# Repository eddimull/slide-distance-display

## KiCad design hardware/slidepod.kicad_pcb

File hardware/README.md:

# SlidePod: wireless trombone slide sensor

A single clip-on pod for the stationary inner slide. It measures slide extension with a
VL53L1X time-of-flight sensor and pitch with an LSM6DS3TR-C accelerometer that picks up
the slide tube's vibration (rev 0.2; rev 0.1 used a piezo contact pickup). It sends position,
pitch and partial over BLE to the Flutter app. There is no screen and no wire to the bell.

## Mechanical constraint that shapes the board

The VL53L1X emits **perpendicular to the PCB**. For the beam to run down the slide, the
board stands as a thin "fin" perpendicular to the slide tubes:

```
        side view (slide runs left → right)

            ┌──┐  ← antenna end (top, away from brass)
            │  │
     PCB →  │  │──►  ToF beam toward the reflector tab on the outer handle brace
   (fin)    │  │
            │▓▓│  ← battery behind the board
     ═══════╧══╧═════════ inner slide tube (clamp at bottom)
```

- The ToF sits on the **front face** with nothing taller than it nearby. The ESP32 module,
  USB-C, switch and battery connector go on the back or sides.
- The module antenna sits at the top edge, as far from the brass as possible, with copper
  keep-out on all layers under and around it per the Espressif guidelines.
- The accelerometer is soldered to the board, which the clamp holds against the tube, so the
  tube's vibration reaches it through the mount. No wired pickup.

Current outline (rev 0.2): **32 × 26 mm**, 4-layer, 1.0 mm thick, **double-sided assembly** (the front holds only what must be seen or reached; the rest is on the back). Rev 0.1 was 30 × 50 mm, single-sided. Ordering steps: `fab/JLCPCB_ORDER.md`.

## Block diagram

```
USB-C ─ESD─┬─ D+/D- ──────────────────────────────► ESP32-S3 GPIO19/20 (native USB)
           └─ VBUS ─┬─► MCP73831 ──► VBAT ─┐
                    │                       ├─(power path)─► SW ─► VSYS ─► ME6211 ─► 3V3
                    └──────── Schottky ─────┘   P-FET from VBAT, gated by VBUS
JST-PH (1S LiPo with protection PCB) ─► VBAT

3V3 ─► ESP32-S3-MINI-1, VL53L1X, LSM6DS3TR-C, status LEDs
```

## Pin map (ESP32-S3-MINI-1)

| Net | GPIO | Notes |
|---|---|---|
| VBAT_SENSE | 2 | ADC1_CH1, 1M/1M divider from VBAT + 100 nF (about 2 µA drain) |
| TOF_INT | 4 | VL53L1X GPIO1 (open-drain, 10k pull-up) |
| TOF_XSHUT | 5 | 10k pull-up; drive low to power the sensor down |
| I2C_SDA | 8 | 4.7k pull-up |
| I2C_SCL | 9 | 4.7k pull-up |
| VBUS_SENSE | 10 | 100k/100k divider from VBUS (5 V → 2.5 V): USB present |
| LED_R / LED_G / LED_B | 11 / 12 / 13 | Three 0603 LEDs, anodes to 3V3, active-low, LEDC PWM |
| USB_D- / USB_D+ | 19 / 20 | Built-in USB-Serial/JTAG for flashing and logs |
| BOOT | 0 | Tactile switch to GND, 10k pull-up |
| EN | EN | 10k pull-up + 1 µF to GND, RESET switch to GND |
| U0TXD / U0RXD | 43 / 44 | Test pads only |

Rev 0.2 moves the sensor and LED lines to the module's right edge and splits I2C into two
buses (the shared bus could not be routed past the LEDs). The pins were reassigned during
layout; `tools/circuit.py` (`esp`) is the source of truth and `src/slidepod/main.cpp` must match:

| Net (rev 0.2) | GPIO | Module pin |
|---|---|---|
| LED_R / LED_G / LED_B | 42 / 41 / 40 | 38 / 37 / 36 |
| TOF_SCL / TOF_SDA | 39 / 38 | 35 / 34 (ToF bus, Wire, 4.7k pull-ups R16/R15) |
| TOF_INT / TOF_XSHUT | 37 / 36 | 33 / 32 |
| IMU_SCL / IMU_SDA | 35 / 48 | 31 / 30 (IMU bus, Wire1, 4.7k pull-ups R20/R19) |
| IMU_INT | 34 | 29 (LSM6DS3TR-C INT1) |

Avoided: strapping pins 3, 45, 46, and ADC2, which conflicts with the radio.

**Why discrete LEDs and not a WS2812:** the system runs at 3.3 V, below the WS2812's
rated supply. A WS2812 also draws about 1 mA even when off, while discrete LEDs on LEDC
draw nothing.

## Circuit blocks

### Power
- **USB-C receptacle (16-pin):** CC1 and CC2 each get 5.1k to GND (UFP, 5 V default).
  USBLC6-2SC6 on D+/D-/VBUS.
- **MCP73831T-2ACI/OT charger:** 4.2 V. R_PROG = 3.3k sets I_chg = 1000 V / 3.3 kΩ ≈ 300 mA
  (about 0.75C for a 400 mAh cell). 4.7 µF on VBUS and on VBAT.
- **Power path:** a Schottky diode from VBUS feeds VSYS. A P-MOSFET (gate to VBUS, 100k
  gate pull-down) connects VBAT to VSYS when USB is absent. This way the charger never
  sees the system load.
- **Power switch:** an SMD slide switch in series with VSYS. The battery still charges with the switch off.
- **Charge LED:** an orange LED on MCP73831 STAT (lit while charging). STAT is not wired to the ESP32, so an unpowered ESP32 is never back-fed through it.
- **ME6211C33 LDO:** 500 mA, enough for ESP32-S3 radio peaks of about 350 mA. 10 µF in and 10 µF out.
- **Battery:** 1S LiPo, 300–500 mAh, **with a protection PCB** (this board doesn't add protection).

### ESP32-S3-MINI-1
- 3V3 on all supply pins, with 10 µF + 100 nF near the module, plus 100 nF at each supply pin group.
- All GND pads go to a solid ground plane on layer 2, stitched with vias.

### VL53L1X
- AVDD and AVDDVCSEL to 3V3, each with 100 nF, plus 4.7 µF bulk.
- I2C address 0x29. XSHUT and GPIO1 as in the pin map.
- Enclosure: an open aperture in front of the sensor, or an IR-transparent cover window
  spaced per ST AN4907. Run crosstalk calibration in firmware if there's a cover.

### Pitch pickup (rev 0.2)
The piezo front end (MCP6001 amplifier, bias divider, clamp diode, anti-alias RC and the J3
solder pads) was removed. The LSM6DS3TR-C on its own I2C bus (0x6A, INT1 on IO34) replaces it:
FIFO-buffered acceleration at up to 6.66 kHz covers the slide-tube fundamentals.

### Indicator and controls
- Three separate 0603 LEDs (red, green, blue), side by side for a light pipe. Series resistors: 1k red (about 1.3 mA), 33 Ω green and blue (about 3–9 mA, depending on Vf at 3.3 V). Balance brightness with PWM in firmware.
  A combined RGB package was dropped because no JLC common-anode part had a pinout I could verify.
- BOOT and RESET tactile switches on the board edge, which the enclosure can expose as pinholes.

### Test points
3V3, VSYS, VBAT, GND, U0TXD, U0RXD (rev 0.2 adds EN and BOOT; TP5 went with the piezo).

## Key parts (JLCPCB / LCSC)

Check live stock and the Basic/Extended label on jlcpcb.com/partdetail/<C#> before ordering.

| Ref | Part | LCSC | Status |
|---|---|---|---|
| U1 | ESP32-S3-MINI-1-N8 | C2913206 | Extended. Alternate: N4R2 C3013941 (PSRAM, not needed) |
| U2 | VL53L1CXV0FY/1 | C190004 | Not yet confirmed on JLC |
| U3 | MCP73831T-2ACI/OT | C424093 | Not yet confirmed |
| U4 | ME6211C33M5G-N | C82942 | Extended. Alternate: AP2112K-3.3 C51118 |
| U6 | USBLC6-2SC6 (ST) | C7519 | Extended |
| J1 | TYPE-C-31-M-12 | C165948 | Extended |
| J2 | JST S2B-PH-SM4-TB | C295747 | Extended |
| SW1/2 | TS-1187A-B-A-B | C318884 | Not yet confirmed |
| SW3 | MSK12C02 | C431540 | Not yet confirmed |
| Q1 | AO3401A | C15127 | Basic |
| D2 | B5819W (CJ) | C8598 | Basic |
| LED1, D3 | KT-0603R red | C2286 | Basic |
| LED2 / LED3 | KT-0603G green / KT-0603B blue | C12624 / C2288 | Extended (no Basic green or blue 0603 LEDs at JLC) |
| R, C | 0402 resistors and capacitors (4.7 µF and 10 µF are 0603) | see `LCSC_R0402` / `LCSC_C` in `tools/circuit.py` | Basic |

## Firmware-facing summary
- I2C @ 400 kHz on GPIO8/9. VL53L1X in Short mode, 20 ms budget, 8×8 ROI.
- Rev 0.2 (build with `-DSLIDEPOD_REV=2`): ToF on Wire (SDA IO38 / SCL IO39); LSM6DS3TR-C (0x6A) on a second bus, Wire1 (SDA IO48 / SCL IO35), INT1 on IO34 for FIFO watermark.
- BLE GATT notify at 50 Hz with about 10 bytes per update. Calibration (offset, length) goes in a writable characteristic.

## Design files and workflow

The schematic and board are **generated** from Python, so changes are reviewable as code:

| File | Role |
|---|---|
| `tools/circuit.py` | **Source of truth:** parts, values, footprints, LCSC numbers, pin-to-net map |
| `tools/gen_sch.py` | Builds `slidepod.kicad_sch` (a net label on every pin, using KiCad library symbols) |
| `tools/gen_pcb.py` | Builds `slidepod.kicad_pcb`: outline, 4-layer stackup, net classes, placement, GND pours |
| `tools/check_net.py` | Checks the exported netlist against `circuit.py`, pin by pin |
| `tools/kicad.sh` | Runs any command in KiCad 10 under Docker (`kicad/kicad:10.0` plus numpy, built from `tools/Dockerfile` on first use) |

```sh
make            # ERC, netlist check against circuit.py, DRC with schematic parity
make pcb        # re-place the board (DISCARDS routing; use only before routing)
make route      # fan-out, Freerouting, finish, stitch (about 30 min)
make fab        # Gerbers, drill, BOM, CPL into fab/
make pdf        # schematic PDF
```

**Placement:** anchor parts (module, ToF, connectors, buttons, LED) have fixed positions
in `ANCHORS`. Everything else is packed to the nearest free spot beside the pins it
connects to. Parts excluded from placement:

- the antenna band (top 6.6 mm), via the module's keep-out rule area
- a 6 × 3.8 mm window around the VL53L1X

### Status (rev 0.1)
- [x] Schematic: ERC clean, netlist matches `circuit.py` (233 pins)
- [x] Board: 30 × 50 mm, 4 layers. Placement, routing, GND/+3V3 planes, stitching.
      **DRC: 0 errors, 0 unconnected, schematic parity clean.**
- [x] Fab outputs in `fab/`: `slidepod-gerbers.zip` (Gerbers + drill), `slidepod-bom.csv`, `slidepod-cpl.csv`
- [x] LCSC numbers on every BOM line
- [ ] Recheck the LSM6DS3TR-C, VL53L1X, MCP73831 and switches on JLC
- [ ] In JLC's assembly preview, check every part's rotation (CPL rotations follow KiCad's zero orientation)

### Stackup and routing pipeline (`make route`)

| Layer | Use |
|---|---|
| F.Cu | Signals + GND pour |
| In1.Cu | Solid GND plane |
| In2.Cu | +3V3 plane |
| B.Cu | Signals + GND pour |

1. `stitch.py fanout`: every +3V3 and GND pad gets a via to its plane plus a short stub, all locked.
2. Freerouting (headless, `.tools/freerouting.jar`) routes the signal nets. GND is excluded.
3. `route.py import` brings the routes back into KiCad.
4. `finish_route.py`: a small grid A* router connects whatever Freerouting left open.
5. `stitch.py finish` removes dangling stubs, adds a 3 mm grid of GND stitching vias, and refills the pours.

`move_part.py REF TARGET PAD` moves one part on the routed board and re-routes its nets
with `finish_route.py`. Rev 0.1 used it once: R6 went next to R7 and C5, so the whole
battery-sense divider sits at the ADC pin. `gen_pcb.py` now places it there itself.

### Review before ordering
- Whether the accelerometer picks up enough of the tube's vibration through the mount is untested. Try it on a real horn.
- The JST-PH battery polarity isn't standard across vendors. Check the battery leads against the `+` marking.
- The VL53L1X needs an open aperture or a proper cover window in the enclosure (ST AN4907).
- Check BLE range with the pod clamped on the horn. Brass near the antenna detunes it.
- A few F.Cu traces run under the ESP32 module, between its center GND pads (solder mask covers them). Espressif allows this outside the antenna area, but rerouting them would remove any risk of shorts.

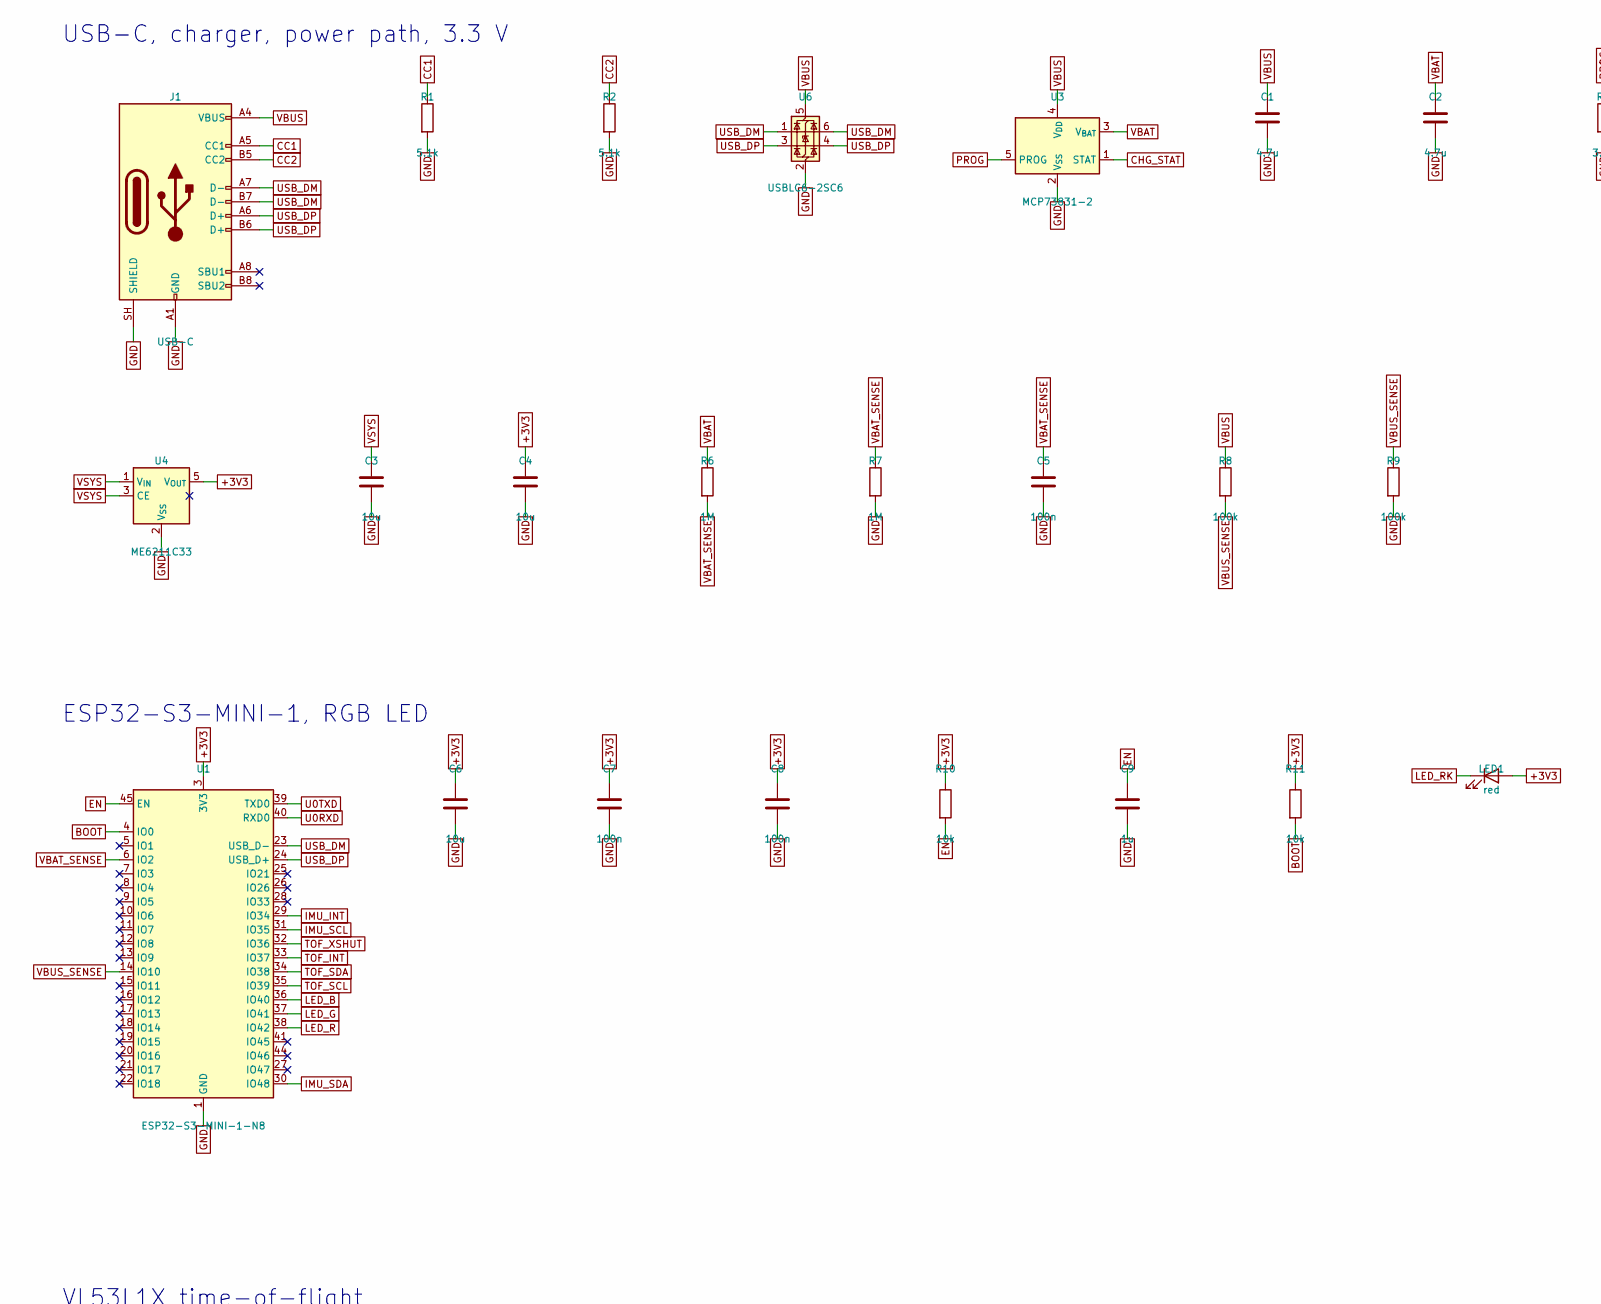
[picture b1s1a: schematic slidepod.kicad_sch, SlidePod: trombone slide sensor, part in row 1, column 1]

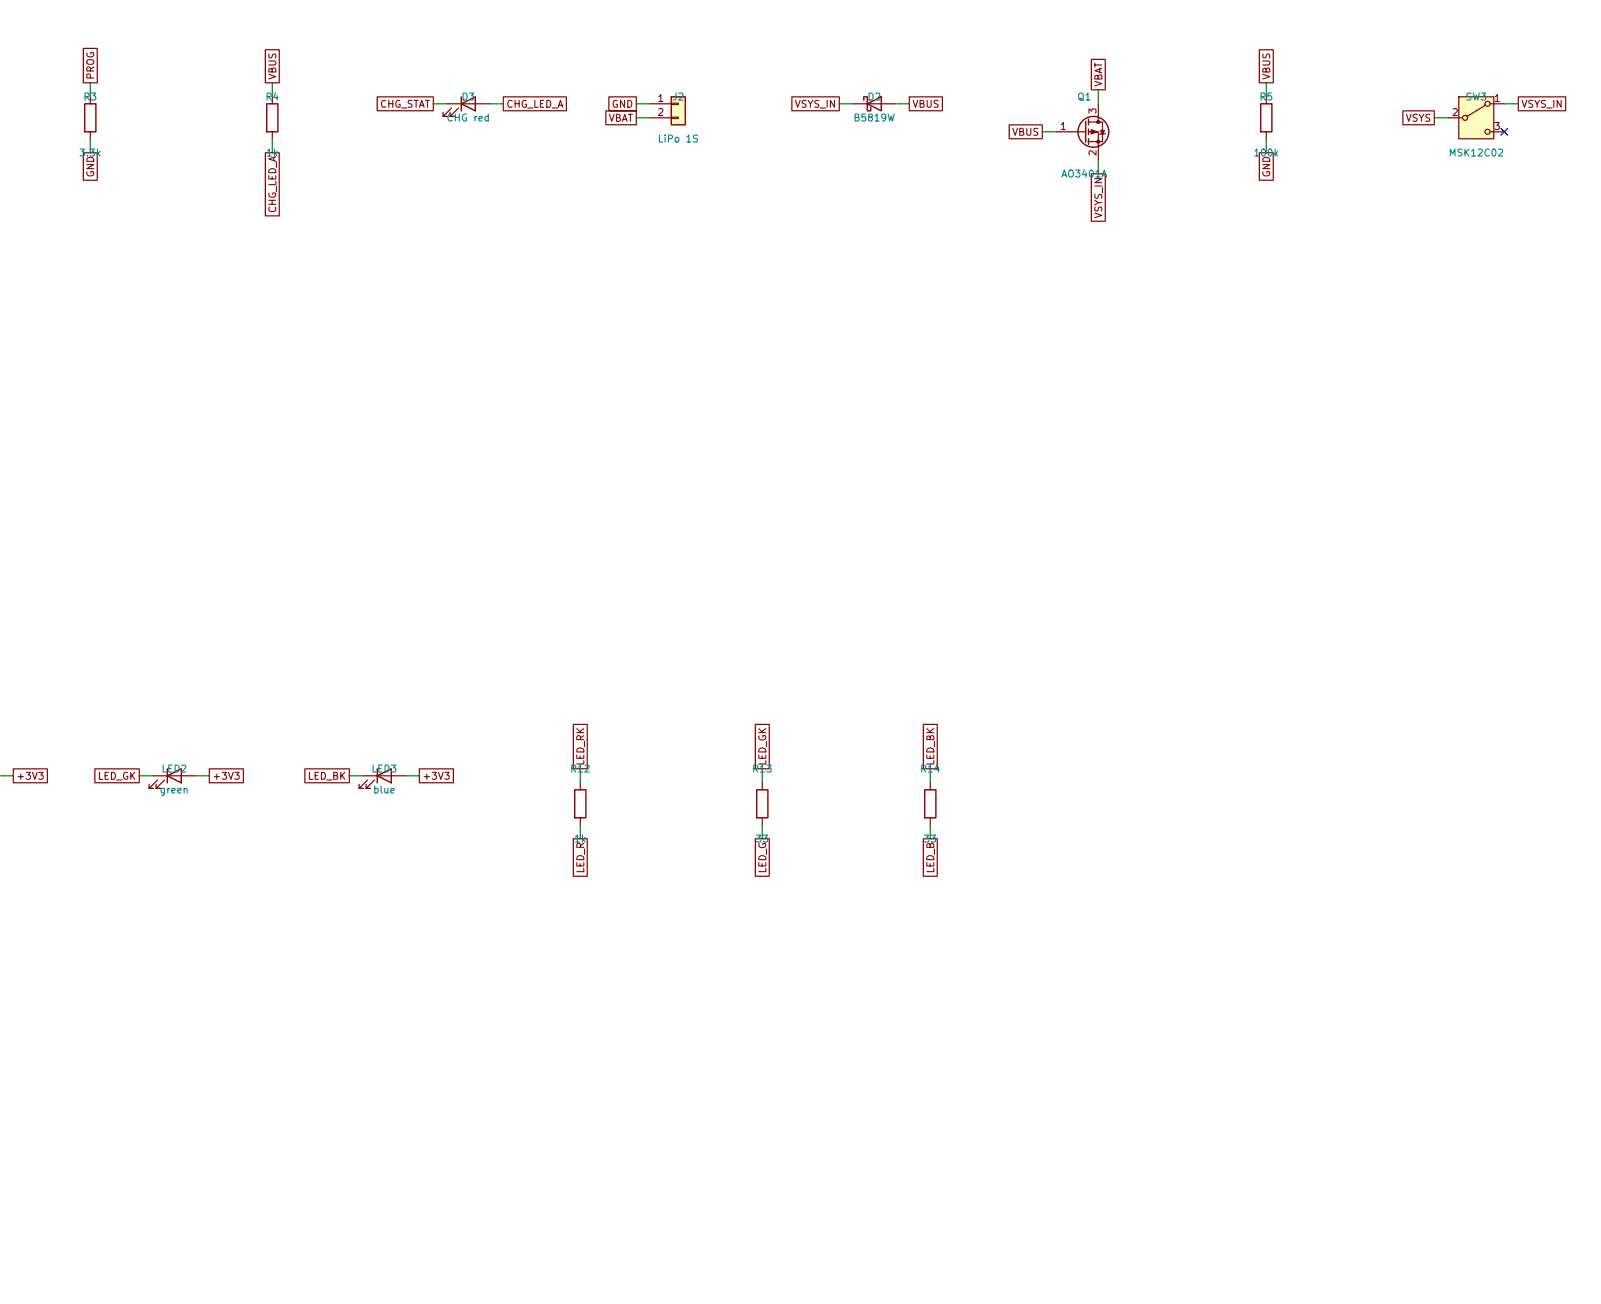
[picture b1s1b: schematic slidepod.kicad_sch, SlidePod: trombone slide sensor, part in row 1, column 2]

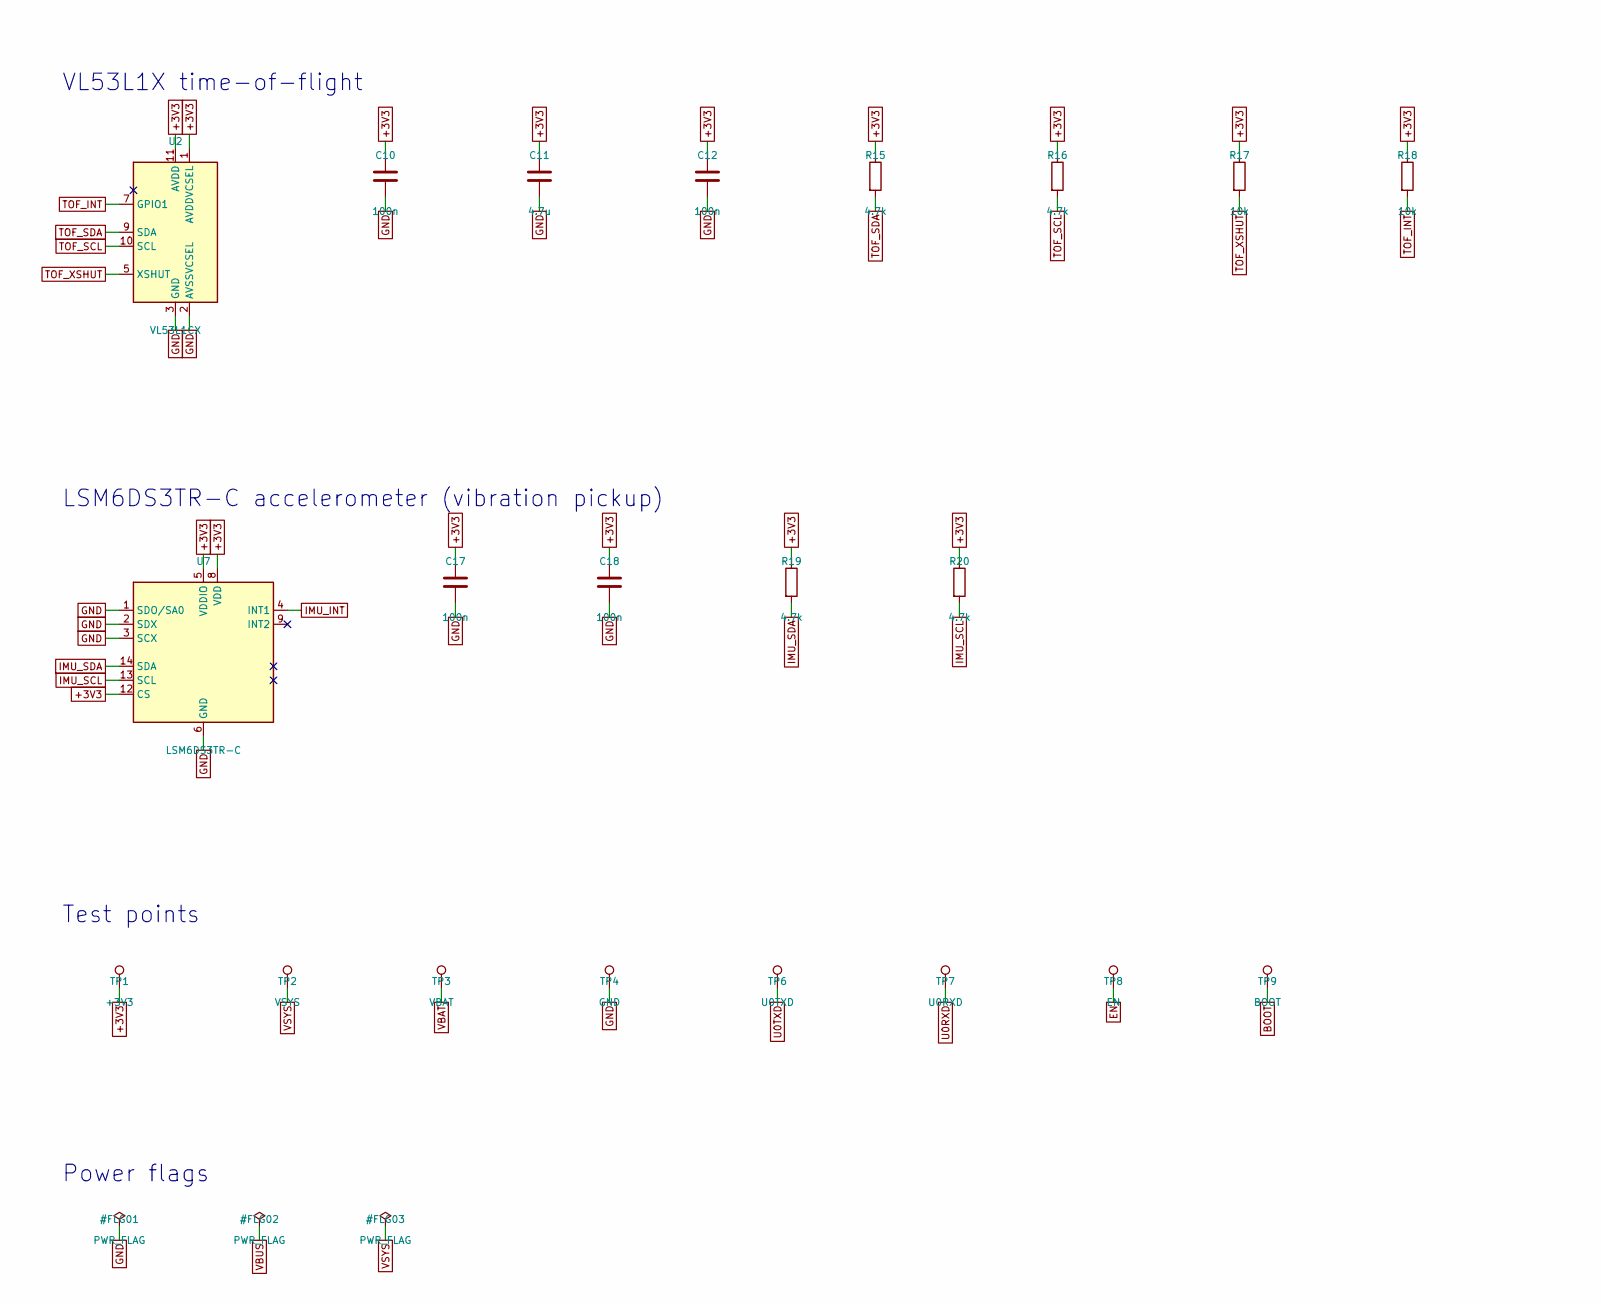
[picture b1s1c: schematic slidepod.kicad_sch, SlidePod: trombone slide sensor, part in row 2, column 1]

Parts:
C1, C2, C11: 4.7u; C_0603_1608Metric; LCSC C19666
C3, C4, C6: 10u; C_0603_1608Metric; LCSC C19702
C5, C7, C8, C10, C12, C17, C18: 100n; C_0402_1005Metric; LCSC C1525
C9: 1u; C_0402_1005Metric; LCSC C52923
D2: B5819W; D_SOD-123; LCSC C8598
D3: CHG red; LED_0603_1608Metric; LCSC C2286
J1: USB-C; USB_C_Receptacle_HRO_TYPE-C-31-M-12; LCSC C165948
J2: LiPo 1S; JST_SH_SM02B-SRSS-TB_1x02-1MP_P1.00mm_Horizontal; LCSC C160402
LED1: red; LED_0603_1608Metric; LCSC C2286
LED2: green; LED_0603_1608Metric; LCSC C12624
LED3: blue; LED_0603_1608Metric; LCSC C2288
Q1: AO3401A; SOT-23; LCSC C15127
R1, R2: 5.1k; R_0402_1005Metric; LCSC C25905
R3: 3.3k; R_0402_1005Metric; LCSC C25890
R4, R12: 1k; R_0402_1005Metric; LCSC C11702
R5, R8, R9: 100k; R_0402_1005Metric; LCSC C25741
R6, R7: 1M; R_0402_1005Metric; LCSC C26083
R10, R11, R17, R18: 10k; R_0402_1005Metric; LCSC C25744
R13, R14: 33; R_0402_1005Metric; LCSC C25105
R15, R16, R19, R20: 4.7k; R_0402_1005Metric; LCSC C25900
SW3: MSK12C02; SW_SPDT_Shouhan_MSK12C02; LCSC C431540
TP1: +3V3; TestPoint_Pad_D1.0mm
TP2: VSYS; TestPoint_Pad_D1.0mm
TP3: VBAT; TestPoint_Pad_D1.0mm
TP4: GND; TestPoint_Pad_D1.0mm
TP6: U0TXD; TestPoint_Pad_D1.0mm
TP7: U0RXD; TestPoint_Pad_D1.0mm
TP8: EN; TestPoint_Pad_D1.0mm
TP9: BOOT; TestPoint_Pad_D1.0mm
U1: ESP32-S3-MINI-1-N8; ESP32-S2-MINI-1; LCSC C2913206
U2: VL53L1CX; ST_VL53L1x; LCSC C190004
U3: MCP73831-2; SOT-23-5; LCSC C424093
U4: ME6211C33; SOT-23-5; LCSC C82942
U6: USBLC6-2SC6; SOT-23-6; LCSC C7519
U7: LSM6DS3TR-C; LGA-14_3x2.5mm_P0.5mm_LayoutBorder3x4y; LCSC C967633

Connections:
+3V3: C4.1, C6.1, C7.1, C8.1, C10.1, C11.1, C12.1, C17.1, C18.1, LED1.2 (A), LED2.2 (A), LED3.2 (A), R10.1, R11.1, R15.1, R16.1, R17.1, R18.1, R19.1, R20.1, TP1.1, U1.3 (3V3), U2.1 (AVDDVCSEL), U2.11 (AVDD), U4.5 (V_{OUT}), U7.5 (VDDIO), U7.8 (VDD), U7.12 (CS)
BOOT: R11.2, TP9.1, U1.4 (IO0)
CC1: J1.A5 (CC1), R1.1
CC2: J1.B5 (CC2), R2.1
CHG_LED_A: D3.2 (A), R4.2
CHG_STAT: D3.1 (K), U3.1 (STAT)
EN: C9.1, R10.2, TP8.1, U1.45 (EN)
GND: C1.2, C2.2, C3.2, C4.2, C5.2, C6.2, C7.2, C8.2, C9.2, C10.2, C11.2, C12.2, C17.2, C18.2, J1.A1 (GND), J1.A12 (GND), J1.B1 (GND), J1.B12 (GND), J1.SH (SHIELD), J2.1, R1.2, R2.2, R3.2, R5.2, R7.2, R9.2, TP4.1, U1.1 (GND), U1.2 (GND), U1.42 (GND), U1.43 (GND), U1.46 (GND), U1.47 (GND), U1.48 (GND), U1.49 (GND), U1.50 (GND), U1.51 (GND), U1.52 (GND), U1.53 (GND), U1.54 (GND), U1.55 (GND), U1.56 (GND), U1.57 (GND), U1.58 (GND), U1.59 (GND), U1.60 (GND), U1.61 (GND), U1.62 (GND), U1.63 (GND), U1.64 (GND), U1.65 (GND), U2.2 (AVSSVCSEL), U2.3 (GND), U2.4 (GND), U2.6 (GND), U2.12 (GND), U3.2 (V_{SS}), U4.2 (V_{SS}), U6.2 (GND), U7.1 (SDO/SA0), U7.2 (SDX), U7.3 (SCX), U7.6 (GND), U7.7 (GND)
IMU_INT: U1.29 (IO34), U7.4 (INT1)
IMU_SCL: R20.2, U1.31 (IO35), U7.13 (SCL)
IMU_SDA: R19.2, U1.30 (IO48), U7.14 (SDA)
LED_B: R14.2, U1.36 (IO40)
LED_BK: LED3.1 (K), R14.1
LED_G: R13.2, U1.37 (IO41)
LED_GK: LED2.1 (K), R13.1
LED_R: R12.2, U1.38 (IO42)
LED_RK: LED1.1 (K), R12.1
PROG: R3.1, U3.5 (PROG)
TOF_INT: R18.2, U1.33 (IO37), U2.7 (GPIO1)
TOF_SCL: R16.2, U1.35 (IO39), U2.10 (SCL)
TOF_SDA: R15.2, U1.34 (IO38), U2.9 (SDA)
TOF_XSHUT: R17.2, U1.32 (IO36), U2.5 (XSHUT)
U0RXD: TP7.1, U1.40 (RXD0)
U0TXD: TP6.1, U1.39 (TXD0)
USB_DM: J1.A7 (D-), J1.B7 (D-), U1.23 (USB_D-), U6.1 (I/O1), U6.6 (I/O1)
USB_DP: J1.A6 (D+), J1.B6 (D+), U1.24 (USB_D+), U6.3 (I/O2), U6.4 (I/O2)
VBAT: C2.1, J2.2, Q1.3 (D), R6.1, TP3.1, U3.3 (V_{BAT})
VBAT_SENSE: C5.1, R6.2, R7.1, U1.6 (IO2)
VBUS: C1.1, D2.2 (A), J1.A4 (VBUS), J1.A9 (VBUS), J1.B4 (VBUS), J1.B9 (VBUS), Q1.1 (G), R4.1, R5.1, R8.1, U3.4 (V_{DD}), U6.5 (VBUS)
VBUS_SENSE: R8.2, R9.1, U1.14 (IO10)
VSYS: C3.1, SW3.2 (B), TP2.1, U4.1 (V_{IN}), U4.3 (CE)
VSYS_IN: D2.1 (K), Q1.2 (S), SW3.1 (A)

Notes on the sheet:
USB-C, charger, power path, 3.3 V
ESP32-S3-MINI-1, RGB LED
VL53L1X time-of-flight
LSM6DS3TR-C accelerometer (vibration pickup)
Test points
Power flags

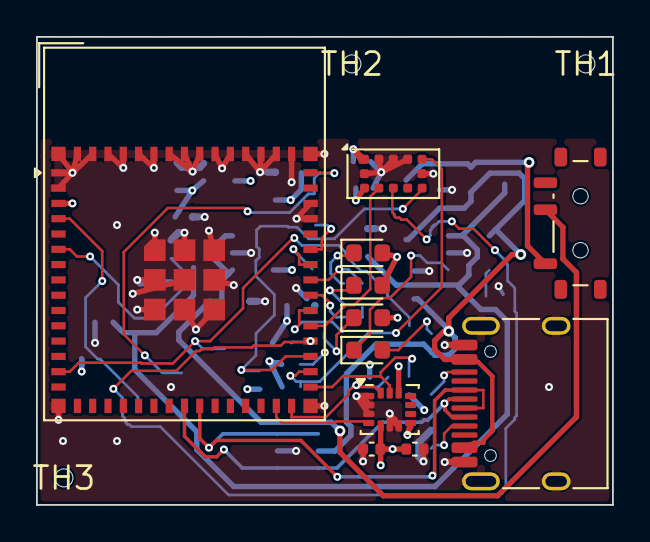
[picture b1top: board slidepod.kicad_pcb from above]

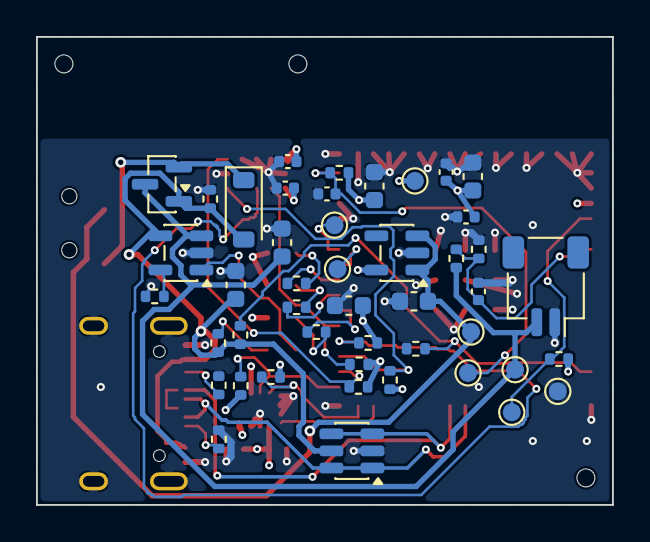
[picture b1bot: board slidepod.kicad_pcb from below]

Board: 4 copper layers, 32.0 x 26.0 mm, 60 parts (46 on the bottom side), 32 nets.

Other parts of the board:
TH1, TH2, TH3: (no value)

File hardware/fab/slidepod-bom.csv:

Comment,Designator,Footprint,LCSC Part #
4.7u,"C1,C11,C2",C_0603_1608Metric,C19666
100n,"C10,C12,C17,C18,C5,C7,C8",C_0402_1005Metric,C1525
10u,"C3,C4,C6",C_0603_1608Metric,C19702
1u,C9,C_0402_1005Metric,C52923
B5819W,D2,D_SOD-123,C8598
CHG red,"D3,LED1",LED_0603_1608Metric,C2286
USB-C,J1,USB_C_Receptacle_HRO_TYPE-C-31-M-12,C165948
LiPo 1S,J2,JST_SH_SM02B-SRSS-TB_1x02-1MP_P1.00mm_Horizontal,C160402
green,LED2,LED_0603_1608Metric,C12624
blue,LED3,LED_0603_1608Metric,C2288
AO3401A,Q1,SOT-23,C15127
5.1k,"R1,R2",R_0402_1005Metric,C25905
10k,"R10,R11,R17,R18",R_0402_1005Metric,C25744
1k,"R12,R4",R_0402_1005Metric,C11702
33,"R13,R14",R_0402_1005Metric,C25105
4.7k,"R15,R16,R19,R20",R_0402_1005Metric,C25900
3.3k,R3,R_0402_1005Metric,C25890
100k,"R5,R8,R9",R_0402_1005Metric,C25741
1M,"R6,R7",R_0402_1005Metric,C26083
MSK12C02,SW3,SW_SPDT_Shouhan_MSK12C02,C431540
ESP32-S3-MINI-1-N8,U1,ESP32-S2-MINI-1,C2913206
VL53L1CX,U2,ST_VL53L1x,C190004
MCP73831-2,U3,SOT-23-5,C424093
ME6211C33,U4,SOT-23-5,C82942
USBLC6-2SC6,U6,SOT-23-6,C7519
LSM6DS3TR-C,U7,LGA-14_3x2.5mm_P0.5mm_LayoutBorder3x4y,C967633

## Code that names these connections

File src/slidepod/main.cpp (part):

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
// ── Pin assignments ──────────────────────────────────────────────────────
#ifdef WOKWI_SIM
  static constexpr int PIN_LED_R     = 25;
  static constexpr int PIN_LED_G     = 26;
  static constexpr int PIN_LED_B     = 27;
  static constexpr int PIN_BOOT      = 0;
#else
  // Real SlidePod hardware (ESP32-S3-MINI-1). Build with -DSLIDEPOD_REV=2 for rev 0.2 boards.
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  // rev 0.2 draft map (SDA 37 / SCL 36 / XSHUT 42 / INT 41 / LEDs 40-38 / IMU_INT 35).
  // The source of truth is the `esp` pin map in hardware/tools/circuit.py; keep them in sync.
  // The ToF and the IMU are on separate I2C buses: ToF on Wire (PIN_SDA/PIN_SCL),
  // IMU on Wire1 (PIN_IMU_SDA/PIN_IMU_SCL), each with its own 4.7k pull-ups on the board.
  static constexpr int PIN_LED_R     = 42;
  static constexpr int PIN_LED_G     = 41;
  static constexpr int PIN_LED_B     = 40;
  static constexpr int PIN_SCL       = 39;   // ToF (VL53L1X, 0x29) bus
  static constexpr int PIN_SDA       = 38;
  static constexpr int PIN_TOF_INT   = 37;
  static constexpr int PIN_TOF_XSHUT = 36;
  static constexpr int PIN_IMU_SCL   = 35;   // IMU (LSM6DS3TR-C, 0x6A) bus -> Wire1
  static constexpr int PIN_IMU_SDA   = 48;
  static constexpr int PIN_IMU_INT   = 34;   // LSM6DS3TR-C INT1
  #else
  // rev 0.1
  static constexpr int PIN_SDA       = 8;
  static constexpr int PIN_SCL       = 9;
  static constexpr int PIN_TOF_XSHUT = 5;
  static constexpr int PIN_TOF_INT   = 4;
  static constexpr int PIN_LED_R     = 11;
  static constexpr int PIN_LED_G     = 12;
  static constexpr int PIN_LED_B     = 13;
  #endif
  static constexpr int PIN_BOOT      = 0;
  // PIEZO_ADC is GPIO1 = ADC1_CH0 (hard-wired in the DMA config below).
  // Same on rev 0.1 and 0.2 (module pins 6 and 14, hardware/tools/circuit.py).
  static constexpr int PIN_VBAT_SENSE = 2;   // ADC1_CH1, VBAT through 1M/1M
  static constexpr int PIN_VBUS_SENSE = 10;  // VBUS through 100k/100k: USB present
#endif

// ── Piezo pitch detection ────────────────────────────────────────────────
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  adc_digi_init_config_t init = {};
  init.max_store_buf_size = 4096;   // ~64 ms of slack at 16 kHz
  init.conv_num_each_intr = 256;    // bytes per DMA interrupt (64 samples)
  init.adc1_chan_mask     = BIT(0); // ADC1_CH0 = GPIO1
  init.adc2_chan_mask     = 0;

  adc_digi_pattern_config_t pat = {};
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  if (key == last) return;
  last = key;
  // Active-low: 255 - level (255 = steady high = off).
  analogWrite(PIN_LED_R, 255 - r);
  analogWrite(PIN_LED_G, 255 - g);
  analogWrite(PIN_LED_B, 255 - b);
}

static void setRgb(bool r, bool g, bool b) {
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  if (last && millis() - last < 2000) return false;
  last = millis();
  uint32_t sum = 0;
  for (int i = 0; i < 16; i++) sum += analogReadMilliVolts(PIN_VBAT_SENSE);
  const float mv = 2.0f * sum / 16;  // undo the 1M/1M divider
  smooth = smooth == 0 ? mv : smooth + 0.2f * (mv - smooth);
  const bool usb = analogReadMilliVolts(PIN_VBUS_SENSE) > 1500;  // 2.5 V on USB
  static uint32_t cvSince = 0;  // when charging reached constant voltage
  static uint8_t cvFrom = 0;    // the estimate then
  uint8_t pct;
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    delay(150);
  }
  // High-Z the LED pins so nothing sinks current through the LEDs asleep.
  pinMode(PIN_LED_R, INPUT);
  pinMode(PIN_LED_G, INPUT);
  pinMode(PIN_LED_B, INPUT);
  Serial.flush();
  esp_sleep_disable_wakeup_source(ESP_SLEEP_WAKEUP_ALL);
  esp_deep_sleep_start();   // doesn't return: only a power cycle wakes it
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  Serial.setTxTimeoutMs(0);
#endif

  pinMode(PIN_LED_R, OUTPUT);
  pinMode(PIN_LED_G, OUTPUT);
  pinMode(PIN_LED_B, OUTPUT);
  pinMode(PIN_BOOT, INPUT_PULLUP);

  setRgb(true, false, false);   // red = booting
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#ifndef WOKWI_SIM
  Wire.begin(PIN_SDA, PIN_SCL);
  // Power-cycle the ToF sensor via XSHUT.
  pinMode(PIN_TOF_XSHUT, OUTPUT);
  digitalWrite(PIN_TOF_XSHUT, LOW);
  delay(10);
  digitalWrite(PIN_TOF_XSHUT, HIGH);
  delay(10);
#endif

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
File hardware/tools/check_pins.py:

"""Cross-check the rev 0.2 firmware pin map against the routed PCB.

Reads U1's (ESP32-S3-MINI-1) pad nets from hardware/slidepod.kicad_pcb, converts module
pin numbers to GPIOs, and checks every PIN_* constant in the SLIDEPOD_REV >= 2 block of
src/slidepod/main.cpp lands on the net it is named for. Exit 1 on any mismatch.
"""
import re, sys, pathlib
root = pathlib.Path(__file__).resolve().parents[2]  # repo root (hardware/tools/ -> ../..)
pcb = (root / "hardware/slidepod.kicad_pcb").read_text(encoding="utf-8")
src = (root / "src/slidepod/main.cpp").read_text(encoding="utf-8")

# ESP32-S3-MINI-1 module pin -> GPIO (datasheet pin table)
MOD = {4: 0, 5: 1, 6: 2, 7: 3, 8: 4, 9: 5, 10: 6, 11: 7, 12: 8, 13: 9, 14: 10, 15: 11, 16: 12,
       17: 13, 18: 14, 19: 15, 20: 16, 21: 17, 22: 18, 23: 19, 24: 20, 25: 21, 26: 26, 27: 47,
       28: 33, 29: 34, 30: 48, 31: 35, 32: 36, 33: 37, 34: 38, 35: 39, 36: 40, 37: 41, 38: 42,
       39: 43, 40: 44, 41: 45, 42: 46}

# U1 footprint block -> pad number -> net name
i = pcb.find('(property "Reference" "U1"')
if i < 0: sys.exit("U1 not found in PCB")
j = pcb.find("\n\t(footprint", i)
u1 = pcb[i:j if j > 0 else len(pcb)]
gpio_net = {}
# each pad block: (pad "N" ... (net "NAME") ... ) -- split on pad starts so nets never leak across pads
for blk in re.split(r'\n\t\t\(pad ', u1)[1:]:
    m = re.match(r'"(\d+)"', blk); n = re.search(r'\(net (?:\d+ )?"([^"]+)"\)', blk)
    if m and n and int(m.group(1)) in MOD: gpio_net[MOD[int(m.group(1))]] = n.group(1)

blk = re.search(r"#if SLIDEPOD_REV >= 2(.*?)#else", src, re.S).group(1)
consts = dict((k, int(v)) for k, v in re.findall(r"constexpr int (PIN_\w+)\s*=\s*(\d+)", blk))
consts["PIN_BOOT"] = int(re.search(r"PIN_BOOT\s*=\s*(\d+);\n\s*// PIEZO", src).group(1))
want = {"PIN_LED_R": "LED_R", "PIN_LED_G": "LED_G", "PIN_LED_B": "LED_B", "PIN_SCL": "TOF_SCL",
        "PIN_SDA": "TOF_SDA", "PIN_TOF_INT": "TOF_INT", "PIN_TOF_XSHUT": "TOF_XSHUT",
        "PIN_IMU_SCL": "IMU_SCL", "PIN_IMU_SDA": "IMU_SDA", "PIN_IMU_INT": "IMU_INT", "PIN_BOOT": "BOOT"}
bad = 0
for k, g in sorted(consts.items()):
    got = gpio_net.get(g, "<unconnected>")
    ok = got == want.get(k)
    bad += not ok
    print(f"{'OK  ' if ok else 'FAIL'} {k:14} GPIO{g:<3} -> PCB net {got:12} (want {want.get(k)})")
used = {n for n in gpio_net.values()}
print("other U1 signal nets:", ", ".join(sorted(f"IO{g}={n}" for g, n in gpio_net.items()
      if n not in want.values() and not n.startswith("unconnected"))))
sys.exit(1 if bad else 0)

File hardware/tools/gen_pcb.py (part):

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    "R5": ("pad", "Q1", "1"),
    "R6": ("pad", "R7", "1"),   # keep the battery-sense divider together at the ADC pin
    "TP1": (2.0, 8.0), "TP2": (4.0, 8.0), "TP3": (6.0, 8.0), "TP4": (2.0, 10.0),
    # UART pads beside the module's U0TXD/U0RXD pins (39/40): far left, their traces ran
    # down the module's right edge and blocked the sensor/LED pins.
    "TP6": (14.3, 12.9), "TP7": (14.3, 11.4), "TP8": (2.0, 12.0),
    "TP9": (4.0, 12.0),
}

# Back parts whose orientation matters: ref -> (pad, direction of that pad from the part centre).
# D2 stands with VSYS_IN up, beside Q1's VSYS_IN pin, and VBUS down toward Q1's gate and the
# charger, so VBUS stays right of the ToF/LED corridor. (VBUS up put it between D2 and Q1; lying
# along x put the VBUS pad, and the VBUS trunk, in the corridor the ToF bus needs.)
PAD_DIR = {"D2": ("1", "-y")}
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
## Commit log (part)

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2024-03-16 init commit
2024-03-17 made the color rectangle sprite. Flickering screen still
2024-03-17 went with my own ultrasonic class
2024-03-20 pausing getting the mic to work
2024-03-20 Got it working.
2024-03-24 added error message on startup
2024-03-24 created a screen state manager color rectangle to render to it
2024-05-25 brought in a kalman filter and got the color sprite to work with it
2024-05-27 cleaned up a little bit and added debug messages
2024-05-27 fixed the velocity cal
2024-05-27 added a fill screen to prevent any extra noise
